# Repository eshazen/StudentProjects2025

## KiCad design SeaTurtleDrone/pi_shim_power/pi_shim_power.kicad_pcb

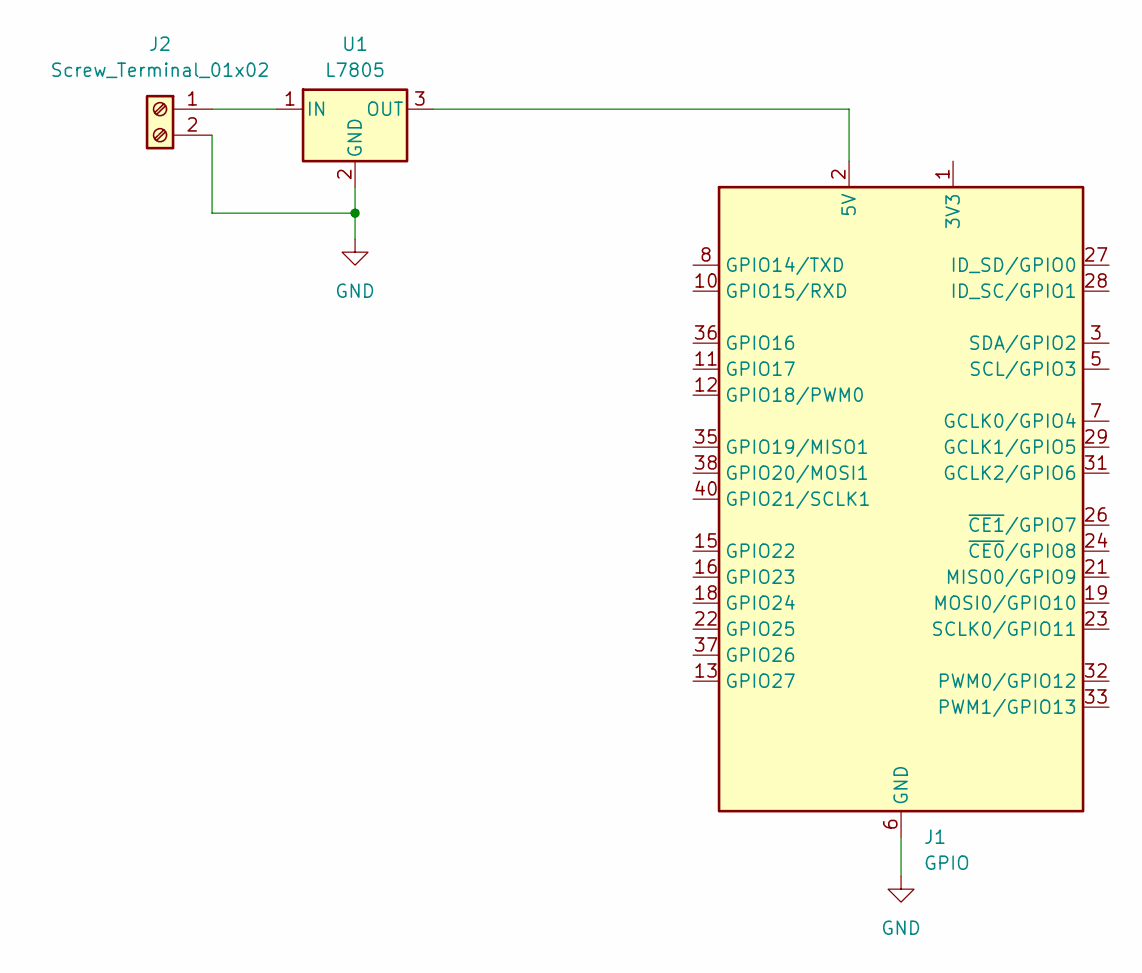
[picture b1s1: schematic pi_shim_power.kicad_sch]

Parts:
J1: GPIO; PinSocket_2x20_P2.54mm_Vertical
J2: Screw_Terminal_01x02; TerminalBlock_MetzConnect_Type055_RT01502HDWU_1x02_P5.00mm_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
U1: L7805; PinHeader_1x03_P2.54mm_Horizontal

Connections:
GND: J1.6 (GND), J1.9 (GND), J1.14 (GND), J1.20 (GND), J1.25 (GND), J1.30 (GND), J1.34 (GND), J1.39 (GND), J2.2, U1.2 (GND)
unnamed: J1.1 (3V3), J1.17 (3V3)
unnamed: J2.1, U1.1 (IN)
unnamed: J1.2 (5V), J1.4 (5V), U1.3 (OUT)

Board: 2 copper layers, 5 parts (1 on the bottom side), 4 nets, no tracks yet.

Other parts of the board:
MH1, MH2: MountingHole_2.7mm_M2.5

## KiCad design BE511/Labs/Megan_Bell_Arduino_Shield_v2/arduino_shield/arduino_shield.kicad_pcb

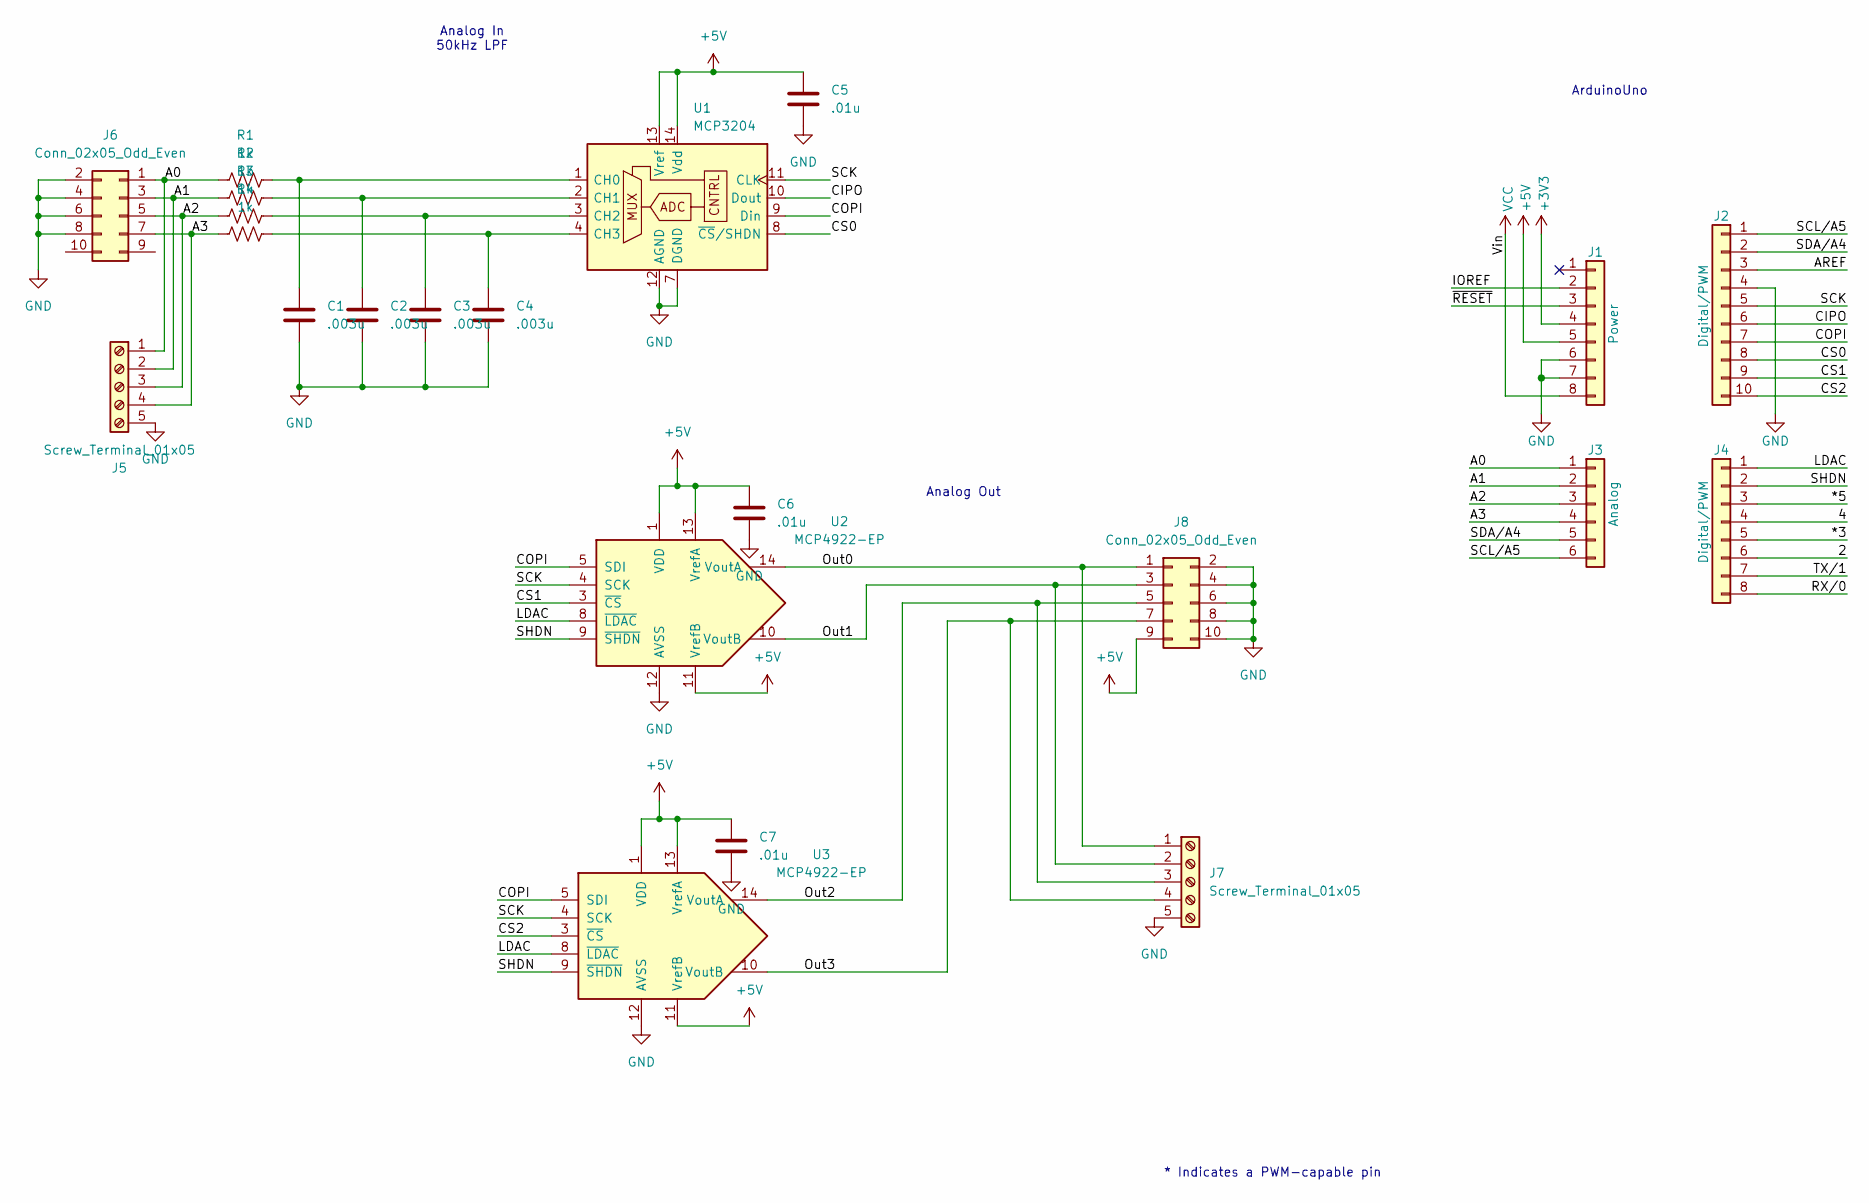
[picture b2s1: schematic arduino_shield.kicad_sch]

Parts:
C1, C2, C3, C4: .003u; C_Disc_D10.0mm_W2.5mm_P5.00mm
C5, C6, C7: .01u; C_Disc_D10.0mm_W2.5mm_P5.00mm
J1: Power; PinSocket_1x08_P2.54mm_Vertical
J2: Digital/PWM; PinSocket_1x10_P2.54mm_Vertical
J3: Analog; PinSocket_1x06_P2.54mm_Vertical
J4: Digital/PWM; PinSocket_1x08_P2.54mm_Vertical
J5, J7: Screw_Terminal_01x05; PinSocket_1x05_P2.54mm_Horizontal
J6, J8: Conn_02x05_Odd_Even; PinSocket_2x05_P2.54mm_Vertical
R1, R2, R3, R4: 1k; R_0805_2012Metric_Pad1.20x1.40mm_HandSolder
U1: MCP3204; DIP-14_W7.62mm
U2, U3: MCP4922-EP; DIP-14_W7.62mm

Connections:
+3V3: J1.4
+5V: C5.1, C6.1, C7.1, J1.5, J8.9, U1.13 (Vref), U1.14 (Vdd), U2.1 (VDD), U2.11 (VrefB), U2.13 (VrefA), U3.1 (VDD), U3.11 (VrefB), U3.13 (VrefA)
/2: J4.6
/4: J4.4
/*3: J4.5
/*5: J4.3
/A0: J3.1, J5.1, J6.1, R1.1
/A1: J3.2, J5.2, J6.3, R2.1
/A2: J3.3, J5.3, J6.5, R3.1
/A3: J3.4, J5.4, J6.7, R4.1
/AREF: J2.3
/CIPO: J2.6, U1.10 (Dout)
/COPI: J2.7, U1.9 (Din), U2.5 (SDI), U3.5 (SDI)
/CS0: J2.8, U1.8 (~CS/SHDN)
/CS1: J2.9, U2.3 (~CS)
/CS2: J2.10, U3.3 (~CS)
/IOREF: J1.2
/LDAC: J4.1, U2.8 (~LDAC), U3.8 (~LDAC)
/Out0: J7.1, J8.1, U2.14 (VoutA)
/Out1: J7.2, J8.3, U2.10 (VoutB)
/Out2: J7.3, J8.5, U3.14 (VoutA)
/Out3: J7.4, J8.7, U3.10 (VoutB)
/RX/0: J4.8
/SCK: J2.5, U1.11 (CLK), U2.4 (SCK), U3.4 (SCK)
/SCL/A5: J2.1, J3.6
/SDA/A4: J2.2, J3.5
/SHDN: J4.2, U2.9 (~SHDN), U3.9 (~SHDN)
/TX/1: J4.7
/~RESET: J1.3
GND: C1.2, C2.2, C3.2, C4.2, C5.2, C6.2, C7.2, J1.6, J1.7, J2.4, J5.5, J6.2, J6.4, J6.6, J6.8, J7.5, J8.2, J8.4, J8.6, J8.8, J8.10, U1.7 (DGND), U1.12 (AGND), U2.12 (AVSS), U3.12 (AVSS)
unnamed: C1.1, R1.2, U1.1 (CH0)
unnamed: C2.1, R2.2, U1.2 (CH1)
unnamed: C3.1, R3.2, U1.3 (CH2)
unnamed: C4.1, R4.2, U1.4 (CH3)
VCC: J1.8

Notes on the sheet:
ArduinoUno
Analog Out
* Indicates a PWM-capable pin
Analog In 50kHz LPF

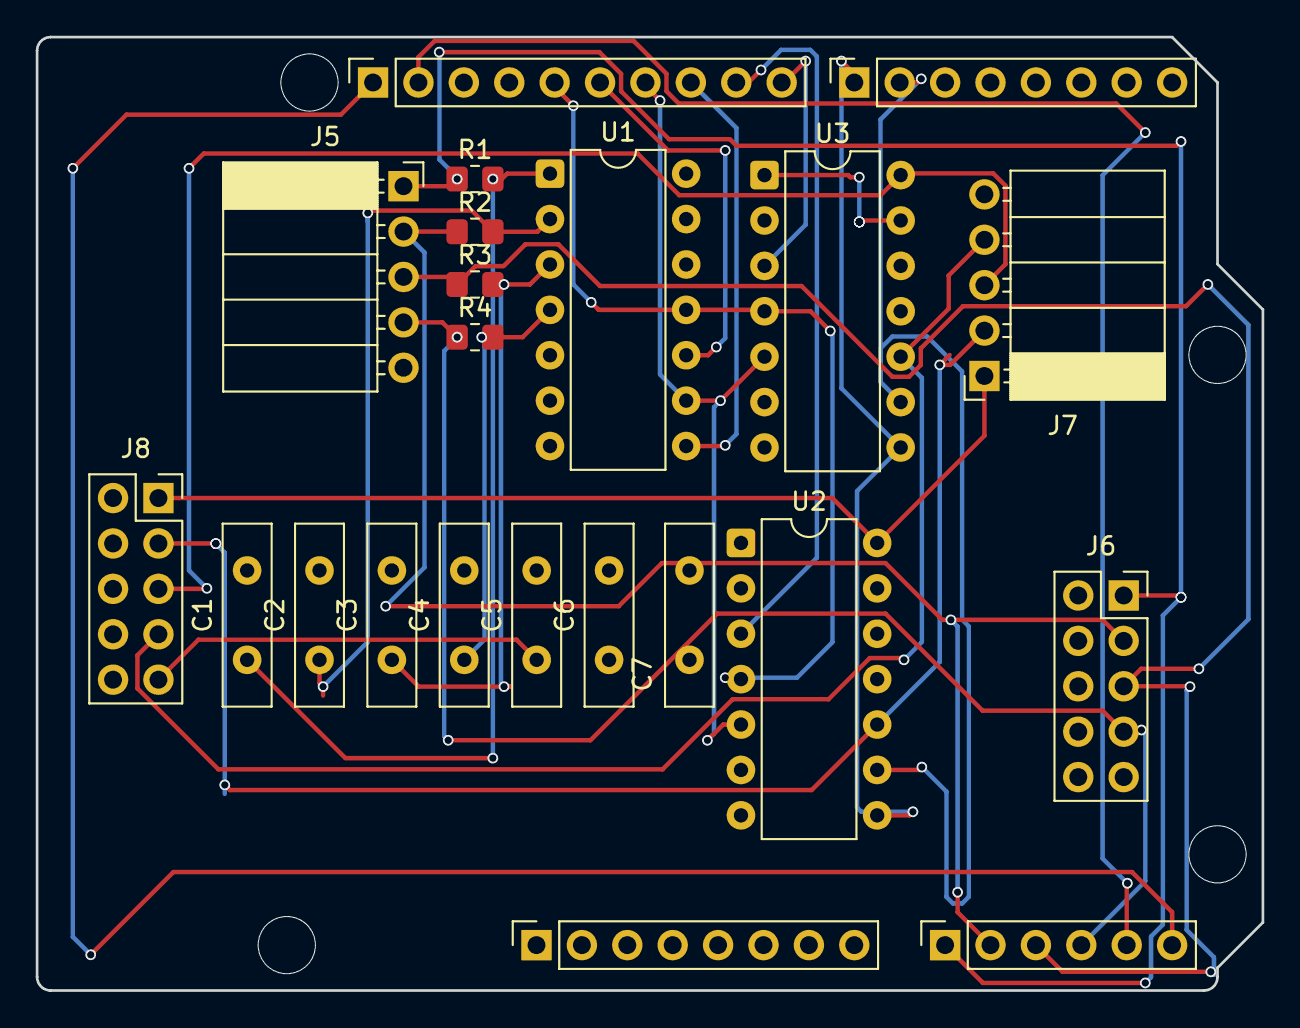
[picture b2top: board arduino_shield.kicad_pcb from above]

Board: 4 copper layers, 68.6 x 53.3 mm, 26 parts (0 on the bottom side), 24 nets.

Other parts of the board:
MH1, MH2, MH3, MH4: MountingHole_3.2mm

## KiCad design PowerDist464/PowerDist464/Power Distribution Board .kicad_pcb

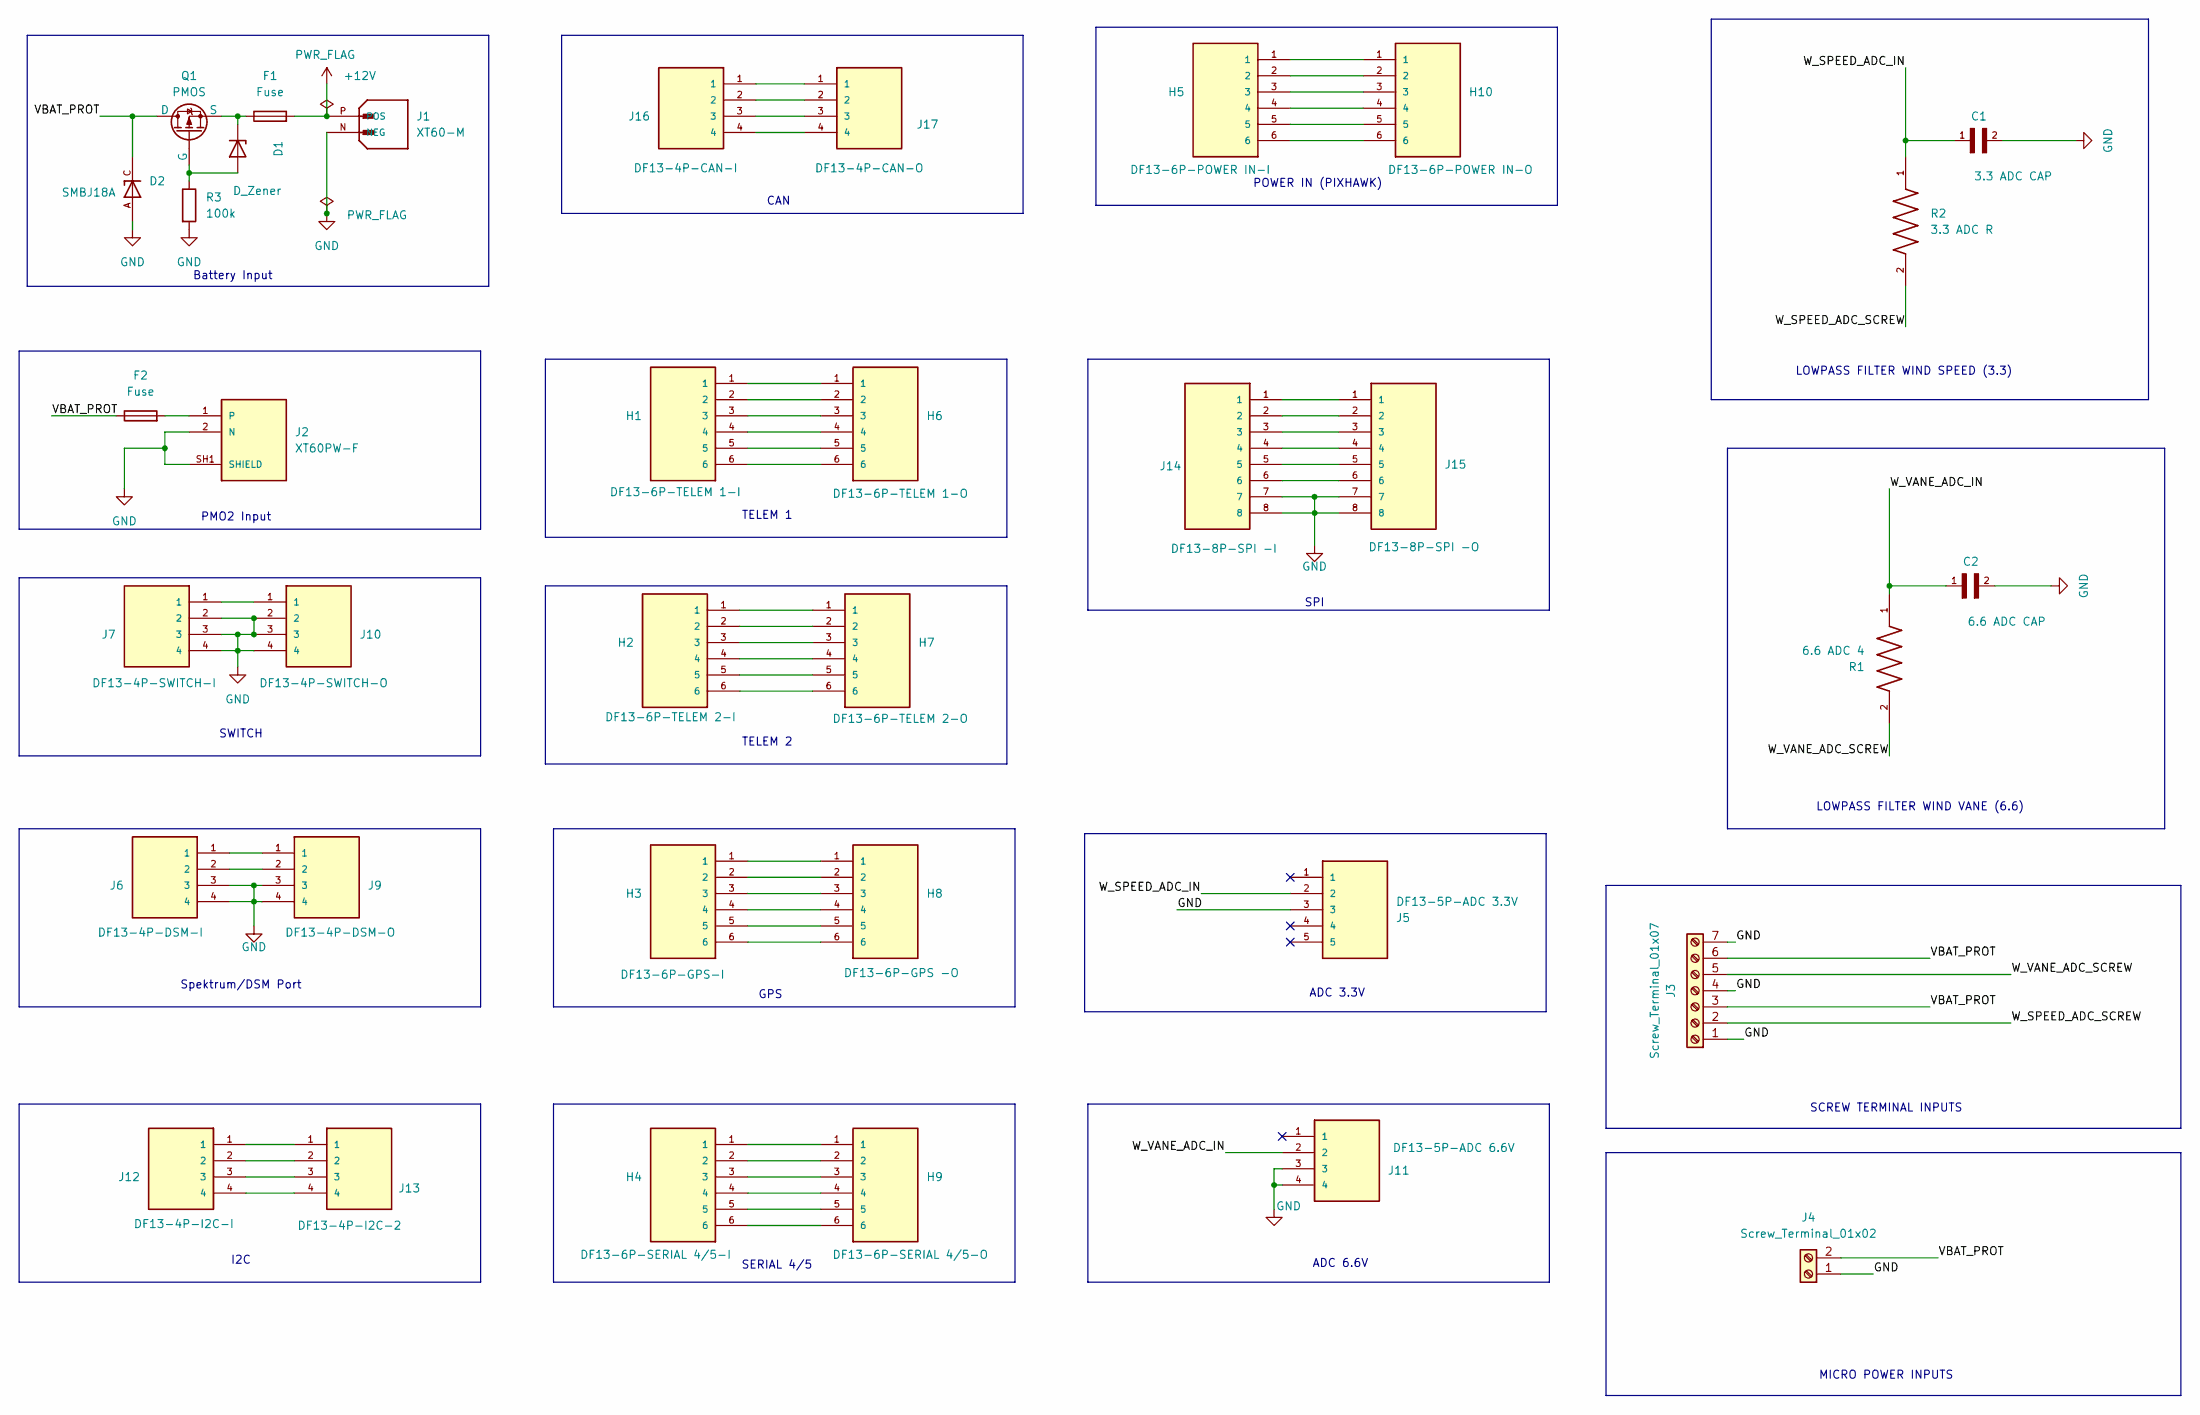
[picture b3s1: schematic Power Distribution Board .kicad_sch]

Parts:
C1: 3.3 ADC CAP; CAPC2012X145N
C2: 6.6 ADC CAP; CAPC2012X145N
D1: D_Zener; DIO_PMEG3020EH_115
D2: SMBJ18A; DIOM4336X265N; PARTREV F2102
F1, F2: Fuse; FUSE_3568-10
H1: DF13-6P-TELEM 1-I; SHDR6W35P0X125_1X6_915X340X430; MOUSER_PART_NUMBER 798-DF13-6P-1.25DSA
H2: DF13-6P-TELEM 2-I; SHDR6W35P0X125_1X6_915X340X430; MOUSER_PART_NUMBER 798-DF13-6P-1.25DSA
H3: DF13-6P-GPS-I; SHDR6W35P0X125_1X6_915X340X430; MOUSER_PART_NUMBER 798-DF13-6P-1.25DSA
H4: DF13-6P-SERIAL 4/5-I; SHDR6W35P0X125_1X6_915X340X430; MOUSER_PART_NUMBER 798-DF13-6P-1.25DSA
H5: DF13-6P-POWER IN-I; SHDR6W35P0X125_1X6_915X340X430; MOUSER_PART_NUMBER 798-DF13-6P-1.25DSA
H6: DF13-6P-TELEM 1-O; SHDR6W35P0X125_1X6_915X340X430; MOUSER_PART_NUMBER 798-DF13-6P-1.25DSA
H7: DF13-6P-TELEM 2-O; SHDR6W35P0X125_1X6_915X340X430; MOUSER_PART_NUMBER 798-DF13-6P-1.25DSA
H8: DF13-6P-GPS -O; SHDR6W35P0X125_1X6_915X340X430; MOUSER_PART_NUMBER 798-DF13-6P-1.25DSA
H9: DF13-6P-SERIAL 4/5-O; SHDR6W35P0X125_1X6_915X340X430; MOUSER_PART_NUMBER 798-DF13-6P-1.25DSA
H10: DF13-6P-POWER IN-O; SHDR6W35P0X125_1X6_915X340X430; MOUSER_PART_NUMBER 798-DF13-6P-1.25DSA
J1: XT60-M; AMASS_XT60-M; PARTREV V1.2
J2: XT60PW-F; AMASS_XT60PW-F; PARTREV 1.2
J3: Screw_Terminal_01x07; TerminalBlock_MaiXu_MX126-5.0-07P_1x07_P5.00mm
J4: Screw_Terminal_01x02; TerminalBlock_MaiXu_MX126-5.0-02P_1x02_P5.00mm
J5: DF13-5P-ADC 3.3V; DF135P125DSA; MOUSER_PART_NUMBER 798-DF13-5P-1.25DSA
J6: DF13-4P-DSM-I; DF134P125DSA; MOUSER_PART_NUMBER 798-DF13-4P-1.25DSA
J7: DF13-4P-SWITCH-I; DF134P125DSA; MOUSER_PART_NUMBER 798-DF13-4P-1.25DSA
J9: DF13-4P-DSM-O; DF134P125DSA; MOUSER_PART_NUMBER 798-DF13-4P-1.25DSA
J10: DF13-4P-SWITCH-O; DF134P125DSA; MOUSER_PART_NUMBER 798-DF13-4P-1.25DSA
J11: DF13-5P-ADC 6.6V; DF134P125DSA; MOUSER_PART_NUMBER 798-DF13-4P-1.25DSA
J12: DF13-4P-I2C-I; DF134P125DSA; MOUSER_PART_NUMBER 798-DF13-4P-1.25DSA
J13: DF13-4P-I2C-2; DF134P125DSA; MOUSER_PART_NUMBER 798-DF13-4P-1.25DSA
J14: DF13-8P-SPI -I; DF138P125DSA; MOUSER_PART_NUMBER 798-DF13-8P-1.25DSA
J15: DF13-8P-SPI -O; DF138P125DSA; MOUSER_PART_NUMBER 798-DF13-8P-1.25DSA
J16: DF13-4P-CAN-I; DF134P125DSA; MOUSER_PART_NUMBER 798-DF13-4P-1.25DSA
J17: DF13-4P-CAN-O; DF134P125DSA; MOUSER_PART_NUMBER 798-DF13-4P-1.25DSA
Q1: PMOS; TO228P998X235-3N-2-V
R1: 6.6 ADC 4; RESC2012X60N
R2: 3.3 ADC R; RESC2012X60N
R3: 100k; R_Axial_DIN0204_L3.6mm_D1.6mm_P5.08mm_Horizontal

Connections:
+12V: F1.2, J1.P (POS)
/VBAT_PROT: D2.C, F2.1, J3.3, J3.6, J4.2, Q1.1 (D)
/W_SPEED_ADC_IN: C1.1, J5.2, R2.1
/W_SPEED_ADC_SCREW: J3.2, R2.2
/W_VANE_ADC_IN: C2.1, J11.2, R1.1
/W_VANE_ADC_SCREW: J3.5, R1.2
GND: C1.2, C2.2, D2.A, J1.N (NEG), J2.2 (N), J2.SH1 (SHIELD), J2.SH2 (SHIELD), J3.1, J3.4, J3.7, J4.1, J5.3, J6.3, J6.4, J7.2, J7.3, J7.4, J9.3, J9.4, J10.2, J10.3, J10.4, J11.3, J11.4, J14.7, J14.8, J15.7, J15.8, R3.2
unnamed: H1.1, H6.1
unnamed: H1.2, H6.2
unnamed: H1.3, H6.3
unnamed: H1.4, H6.4
unnamed: H1.5, H6.5
unnamed: H1.6, H6.6
unnamed: H2.1, H7.1
unnamed: H2.2, H7.2
unnamed: H2.3, H7.3
unnamed: H2.4, H7.4
unnamed: H2.5, H7.5
unnamed: H2.6, H7.6
unnamed: H3.1, H8.1
unnamed: H3.2, H8.2
unnamed: H3.3, H8.3
unnamed: H3.4, H8.4
unnamed: H3.5, H8.5
unnamed: H3.6, H8.6
unnamed: H4.1, H9.1
unnamed: H4.2, H9.2
unnamed: H4.3, H9.3
unnamed: H4.4, H9.4
unnamed: H4.5, H9.5
unnamed: H4.6, H9.6
unnamed: H5.1, H10.1
unnamed: H5.2, H10.2
unnamed: H5.3, H10.3
unnamed: H5.4, H10.4
unnamed: H5.5, H10.5
unnamed: H5.6, H10.6
unnamed: F2.2, J2.1
unnamed: J6.1, J9.1
unnamed: J6.2, J9.2
unnamed: J7.1, J10.1
unnamed: J12.1, J13.1
unnamed: J12.2, J13.2
unnamed: J12.3, J13.3
unnamed: J12.4, J13.4
unnamed: J14.1, J15.1
unnamed: J14.2, J15.2
unnamed: J14.3, J15.3
unnamed: J14.4, J15.4
unnamed: J14.5, J15.5
unnamed: J14.6, J15.6
unnamed: J16.1, J17.1
unnamed: J16.2, J17.2
unnamed: J16.3, J17.3
unnamed: J16.4, J17.4
unnamed: D1.2, Q1.2 (G), R3.1
unnamed: D1.1, F1.1, Q1.3 (S)

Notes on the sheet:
LOWPASS FILTER WIND SPEED (3.3)
SCREW TERMINAL INPUTS
GPS
LOWPASS FILTER WIND VANE (6.6)
I2C
MICRO POWER INPUTS
ADC 3.3V
Battery Input
Spektrum/DSM Port
TELEM 2
SPI
SERIAL 4/5
CAN
SWITCH
TELEM 1
ADC 6.6V
POWER IN (PIXHAWK)
PMO2 Input

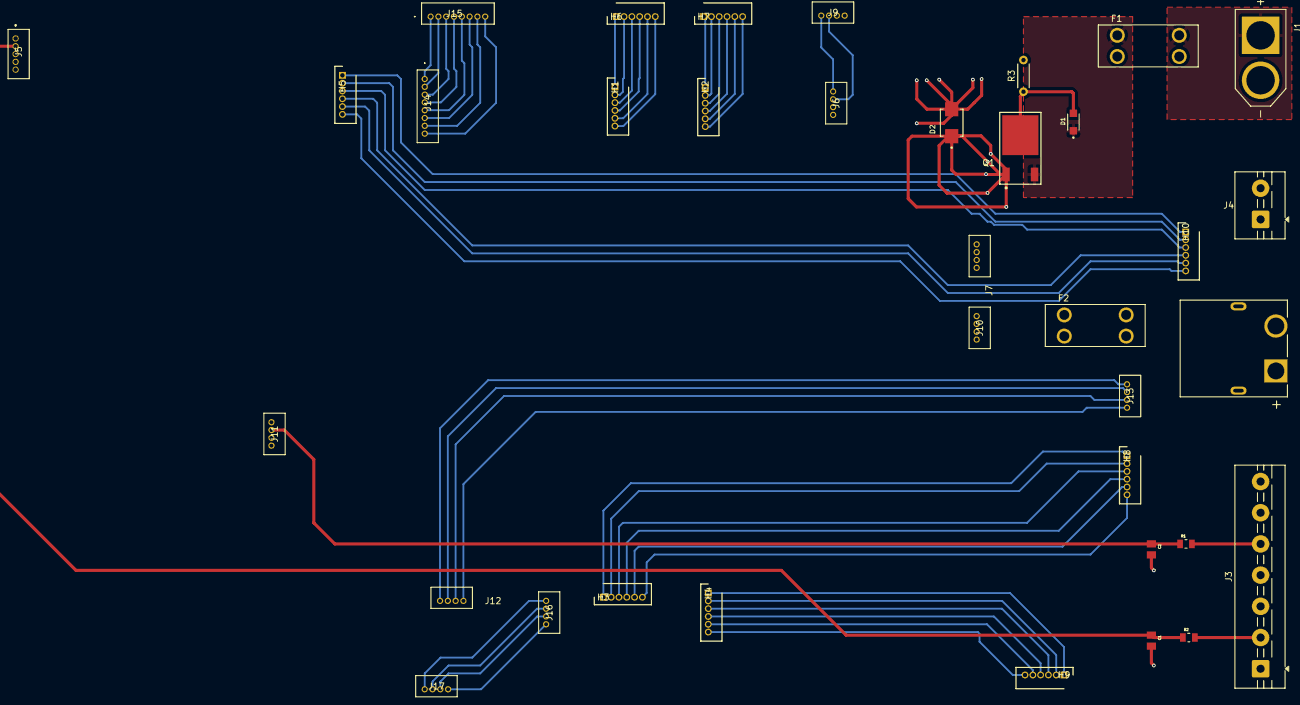
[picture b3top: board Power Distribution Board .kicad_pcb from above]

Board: 4 copper layers, 36 parts (0 on the bottom side), 57 nets.

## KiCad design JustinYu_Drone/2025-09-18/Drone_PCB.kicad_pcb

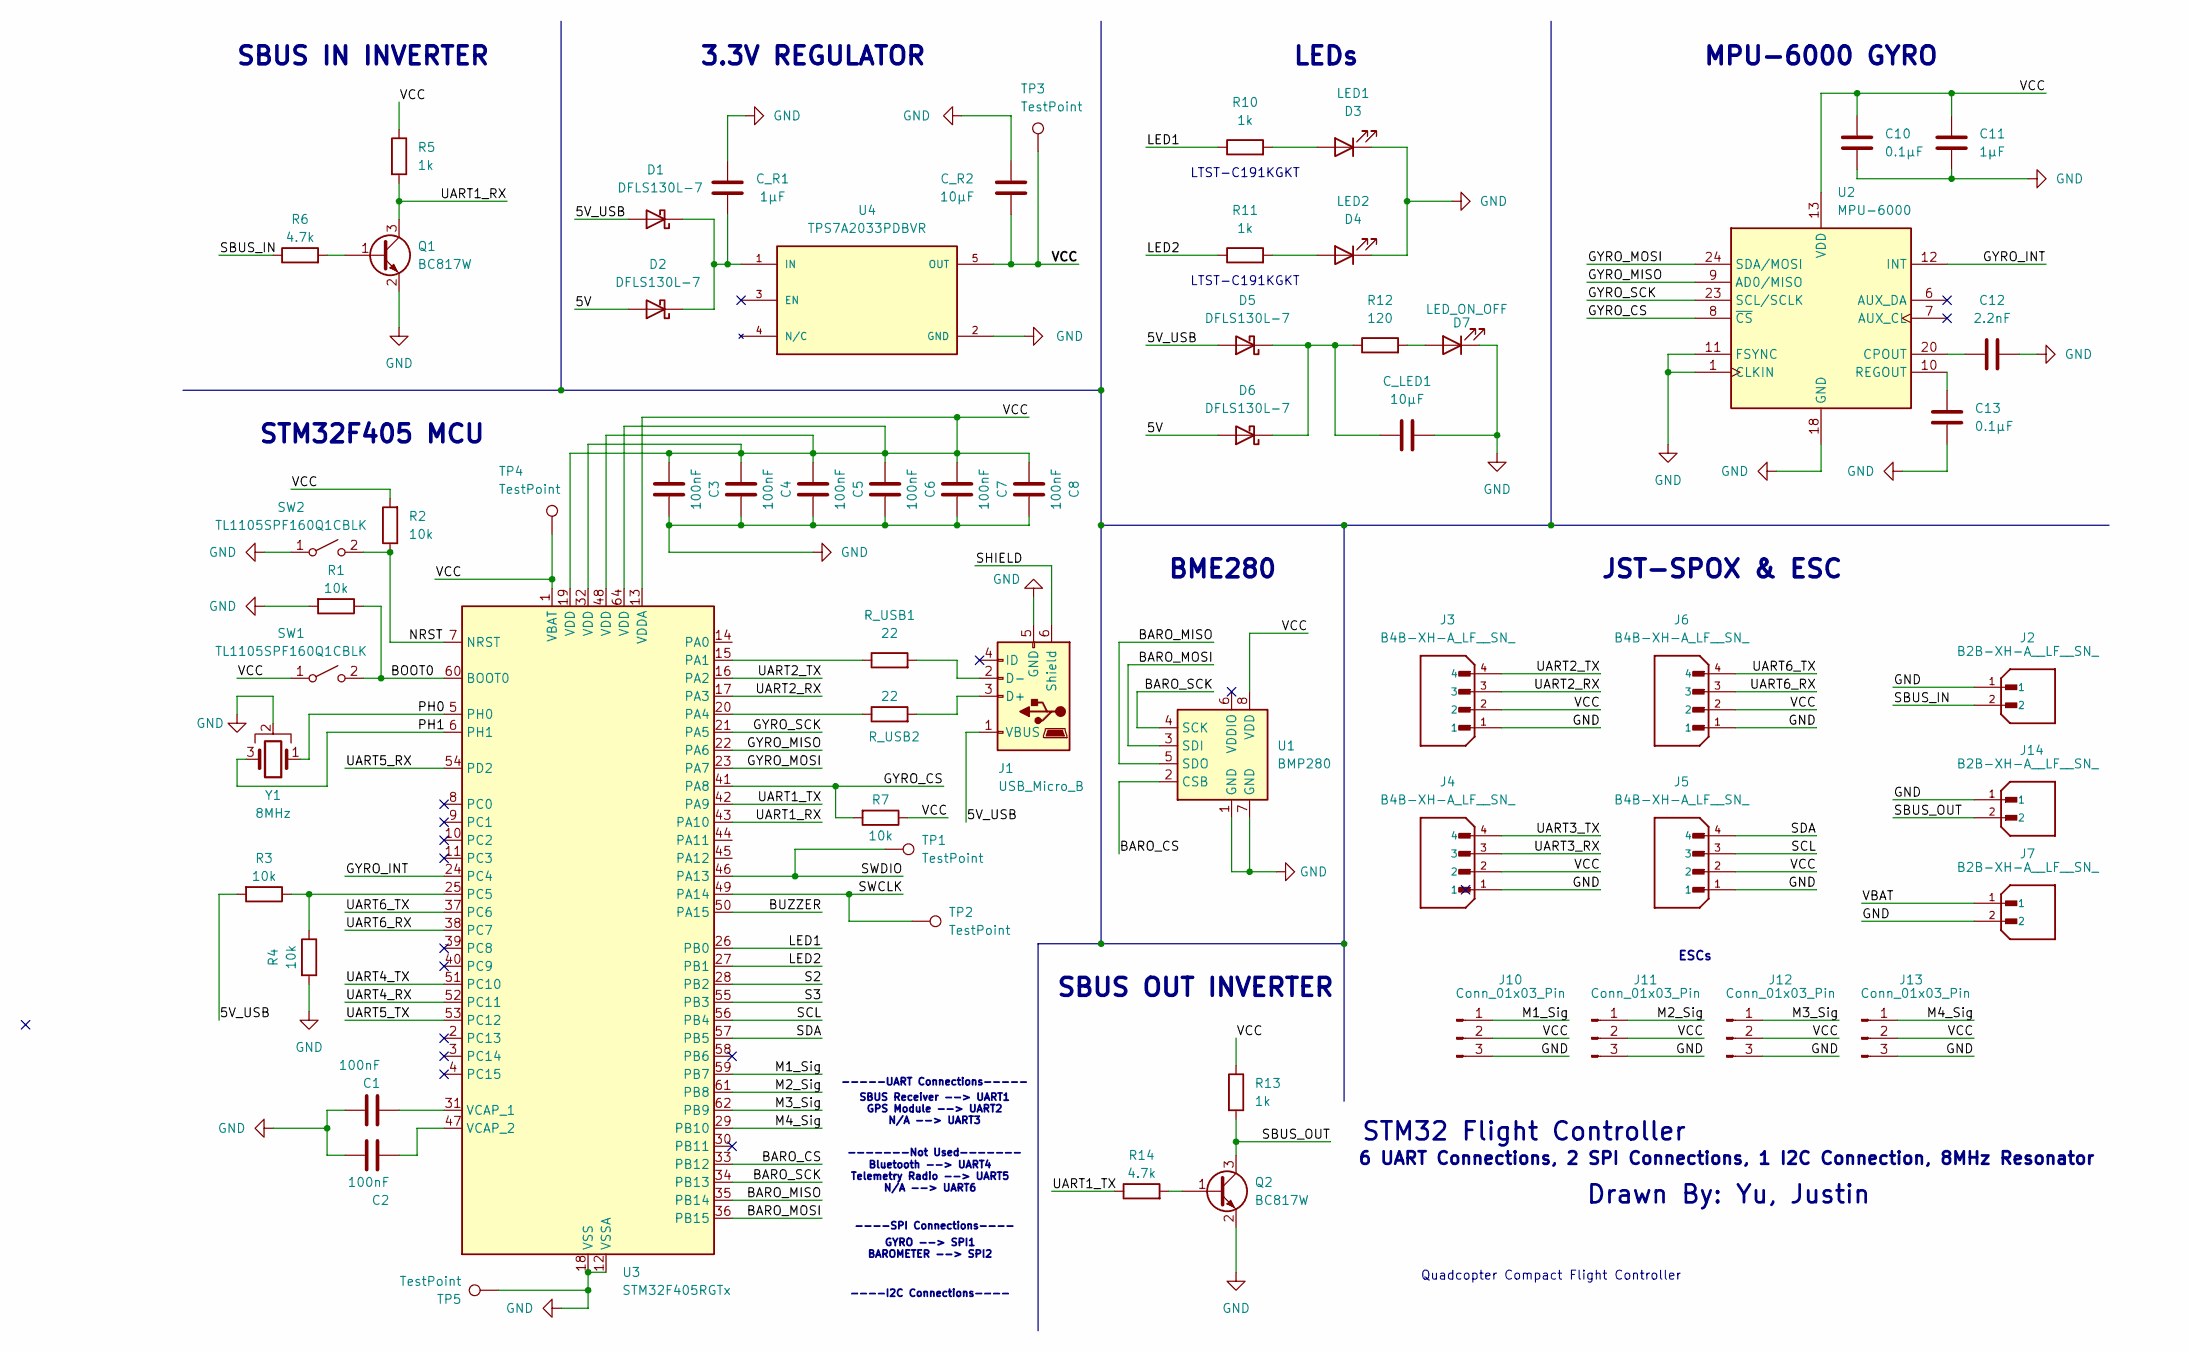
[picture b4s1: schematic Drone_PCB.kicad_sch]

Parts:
C1, C2, C3, C4, C5, C6, C7, C8: 100nF; CC0603KRX7R8BB104
C10, C13: 0.1µF; CC0603KRX7R8BB104
C11: 1µF; CC0603KRX7R8BB104
C12: 2.2nF; CC0603KRX7R8BB104
C_LED1: 10μF; CC0603KRX7R8BB104
C_R1: 1µF; CC0603KRX7R8BB104
C_R2: 10µF; CC0603KRX7R8BB104
D1, D2, D5, D6: DFLS130L-7
D3: LED1; LTST-C191KGKT
D4: LED2; LTST-C191KGKT
D7: LED_ON_OFF; LTST-C191KGKT
J1: USB_Micro_B; USB_C
J2, J14: B2B-XH-A__LF__SN_; PinSocket_1x02_P2.54mm_Vertical; PARTREV N/A
J3, J4, J5, J6: B4B-XH-A_LF__SN_; JST_B4B; PARTREV 7/4/21
J7: B2B-XH-A__LF__SN_; JST_B2B-XH-A__LF__SN_; PARTREV N/A
J10, J11, J12, J13: Conn_01x03_Pin; PinSocket_1x03_P2.54mm_Vertical
Q1, Q2: BC817W
R1, R2, R3, R4, R7: 10k; R_0603_1608Metric_Pad0.98x0.95mm_HandSolder
R5, R10, R11, R13: 1k; R_0603_1608Metric_Pad0.98x0.95mm_HandSolder
R6, R14: 4.7k; R_0603_1608Metric_Pad0.98x0.95mm_HandSolder
R12: 120; R_0603_1608Metric_Pad0.98x0.95mm_HandSolder
R_USB1, R_USB2: 22; R_0603_1608Metric_Pad0.98x0.95mm_HandSolder
SW1, SW2: TL1105SPF160Q1CBLK; KMR221G LFS
TP1, TP2, TP3, TP4, TP5: TestPoint; TestPoint_Pad_1.0x1.0mm
U1: BMP280
U2: MPU-6000; InvenSense_QFN-24_4x4mm_P0.5mm
U3: STM32F405RGTx; LQFP-64_10x10mm_P0.5mm
U4: TPS7A2033PDBVR; PARTREV H
Y1: 8MHz; ABLS-8.000MHZ-B4-T

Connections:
/5V: D2.2 (A), D6.2 (A)
/5V_USB: D1.2 (A), D5.2 (A), J1.1 (VBUS), R3.2
/BARO_CS: U1.2 (CSB), U3.33 (PB12)
/BARO_MISO: U1.5 (SDO), U3.35 (PB14)
/BARO_MOSI: U1.3 (SDI), U3.36 (PB15)
/BARO_SCK: U1.4 (SCK), U3.34 (PB13)
/BOOT0: R1.1, SW1.2 (B), U3.60 (BOOT0)
/BUZZER: U3.50 (PA15)
/GYRO_CS: R7.2, U2.8 (~CS), U3.41 (PA8)
/GYRO_INT: U2.12 (INT), U3.24 (PC4)
/GYRO_MISO: U2.9 (AD0/MISO), U3.22 (PA6)
/GYRO_MOSI: U2.24 (SDA/MOSI), U3.23 (PA7)
/GYRO_SCK: U2.23 (SCL/SCLK), U3.21 (PA5)
/LED1: R10.1, U3.26 (PB0)
/LED2: R11.1, U3.27 (PB1)
/M1_Sig: J10.1, U3.59 (PB7)
/M2_Sig: J11.1, U3.61 (PB8)
/M3_Sig: J12.1, U3.62 (PB9)
/M4_Sig: J13.1, U3.29 (PB10)
/NRST: R2.1, SW2.2 (B), U3.7 (NRST)
/PH0: U3.5 (PH0), Y1.1
/S2: U3.28 (PB2)
/S3: U3.55 (PB3)
/SBUS_IN: J2.2, R6.1
/SBUS_OUT: J14.2, Q2.3 (C), R13.2
/SCL: J5.3, U3.56 (PB4)
/SDA: J5.4, U3.57 (PB5)
/SWCLK: TP2.1, U3.49 (PA14)
/SWDIO: TP1.1, U3.46 (PA13)
/UART1_RX: Q1.3 (C), R5.2, U3.43 (PA10)
/UART1_TX: R14.1, U3.42 (PA9)
/UART2_RX: J3.3, U3.17 (PA3)
/UART2_TX: J3.4, U3.16 (PA2)
/UART3_RX: J4.3
/UART3_TX: J4.4
/UART4_RX: U3.52 (PC11)
/UART4_TX: U3.51 (PC10)
/UART5_RX: U3.54 (PD2)
/UART5_TX: U3.53 (PC12)
/UART6_RX: J6.3, U3.38 (PC7)
/UART6_TX: J6.4, U3.37 (PC6)
/VCC: C3.1, C4.1, C5.1, C6.1, C7.1, C8.2, C10.2, C11.2, C_R2.1, J3.2, J4.2, J5.2, J6.2, J10.2, J11.2, J12.2, J13.2, R2.2, R5.1, R7.1, R13.1, SW1.1 (A), TP3.1, TP4.1, U1.8 (VDD), U2.13 (VDD), U3.1 (VBAT), U3.13 (VDDA), U3.19 (VDD), U3.32 (VDD), U3.48 (VDD), U3.64 (VDD), U4.5 (OUT)
unnamed: C_R1.1, D1.1 (K), D2.1 (K), U4.1 (IN)
unnamed: D3.2 (A), R10.2
unnamed: D4.2 (A), R11.2
unnamed: C_LED1.2, D5.1 (K), D6.1 (K), R12.1
unnamed: D7.2 (A), R12.2
unnamed: J1.3 (D+), R_USB2.2
unnamed: J1.2 (D-), R_USB1.2
unnamed: Q1.1 (B), R6.2
unnamed: Q2.1 (B), R14.2
unnamed: C12.2, U2.20 (CPOUT)
unnamed: C13.2, U2.10 (REGOUT)
unnamed: R_USB1.1, U3.15 (PA1)
unnamed: R_USB2.1, U3.20 (PA4)
unnamed: R3.1, R4.1, U3.25 (PC5)
unnamed: C1.1, U3.31 (VCAP_1)
unnamed: C2.1, U3.47 (VCAP_2)

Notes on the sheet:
LTST-C191KGKT
----SPI Connections----
GYRO --> SPI1 BAROMETER --> SPI2
SBUS OUT INVERTER
6 UART Connections, 2 SPI Connections, 1 I2C Connection, 8MHz Resonator
3.3V REGULATOR
STM32 Flight Controller
Yu, Justin
SBUS Receiver --> UART1 GPS Module --> UART2 N/A --> UART3
-----UART Connections-----
STM32F405 MCU
----I2C Connections----
BME280
Bluetooth --> UART4 Telemetry Radio --> UART5 N/A --> UART6
Quadcopter Compact Flight Controller
LEDs
-------Not Used-------
JST-SPOX & ESC
MPU-6000 GYRO
ESCs
SBUS IN INVERTER
Drawn By:

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
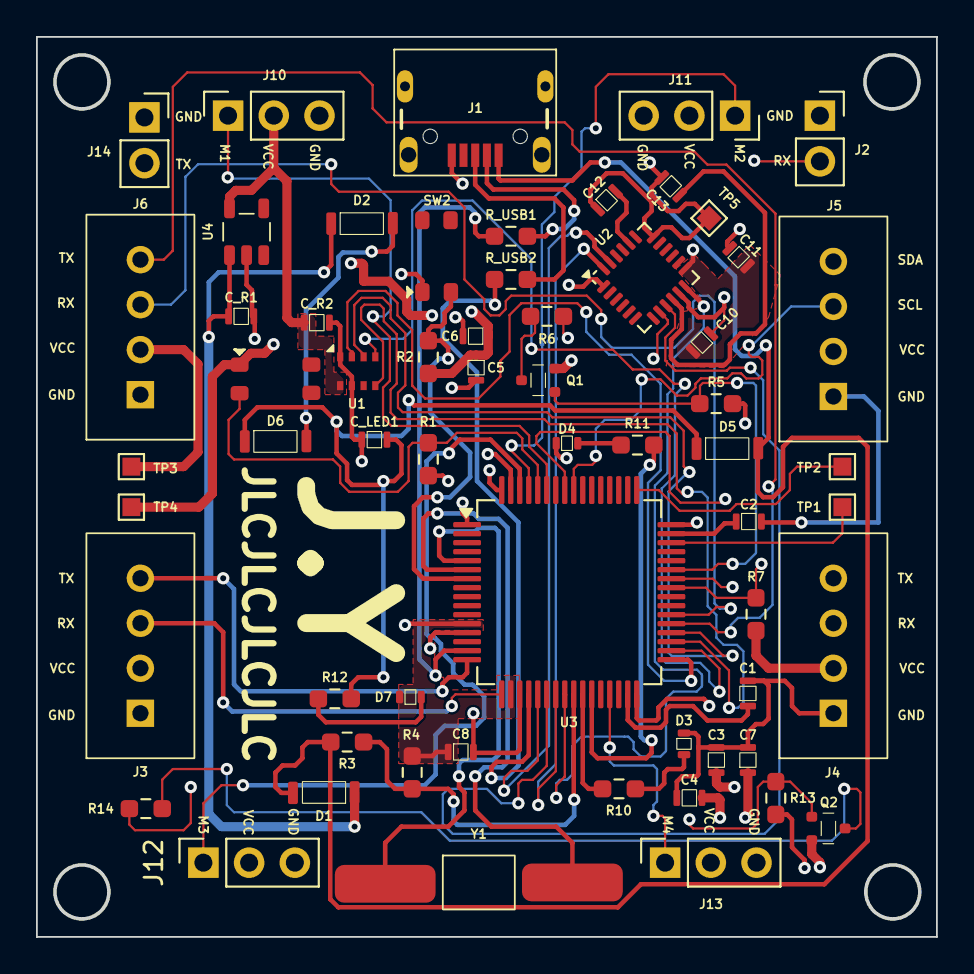
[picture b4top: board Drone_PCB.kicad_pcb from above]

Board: 4 copper layers, 50.0 x 50.0 mm, 61 parts (0 on the bottom side), 51 nets.

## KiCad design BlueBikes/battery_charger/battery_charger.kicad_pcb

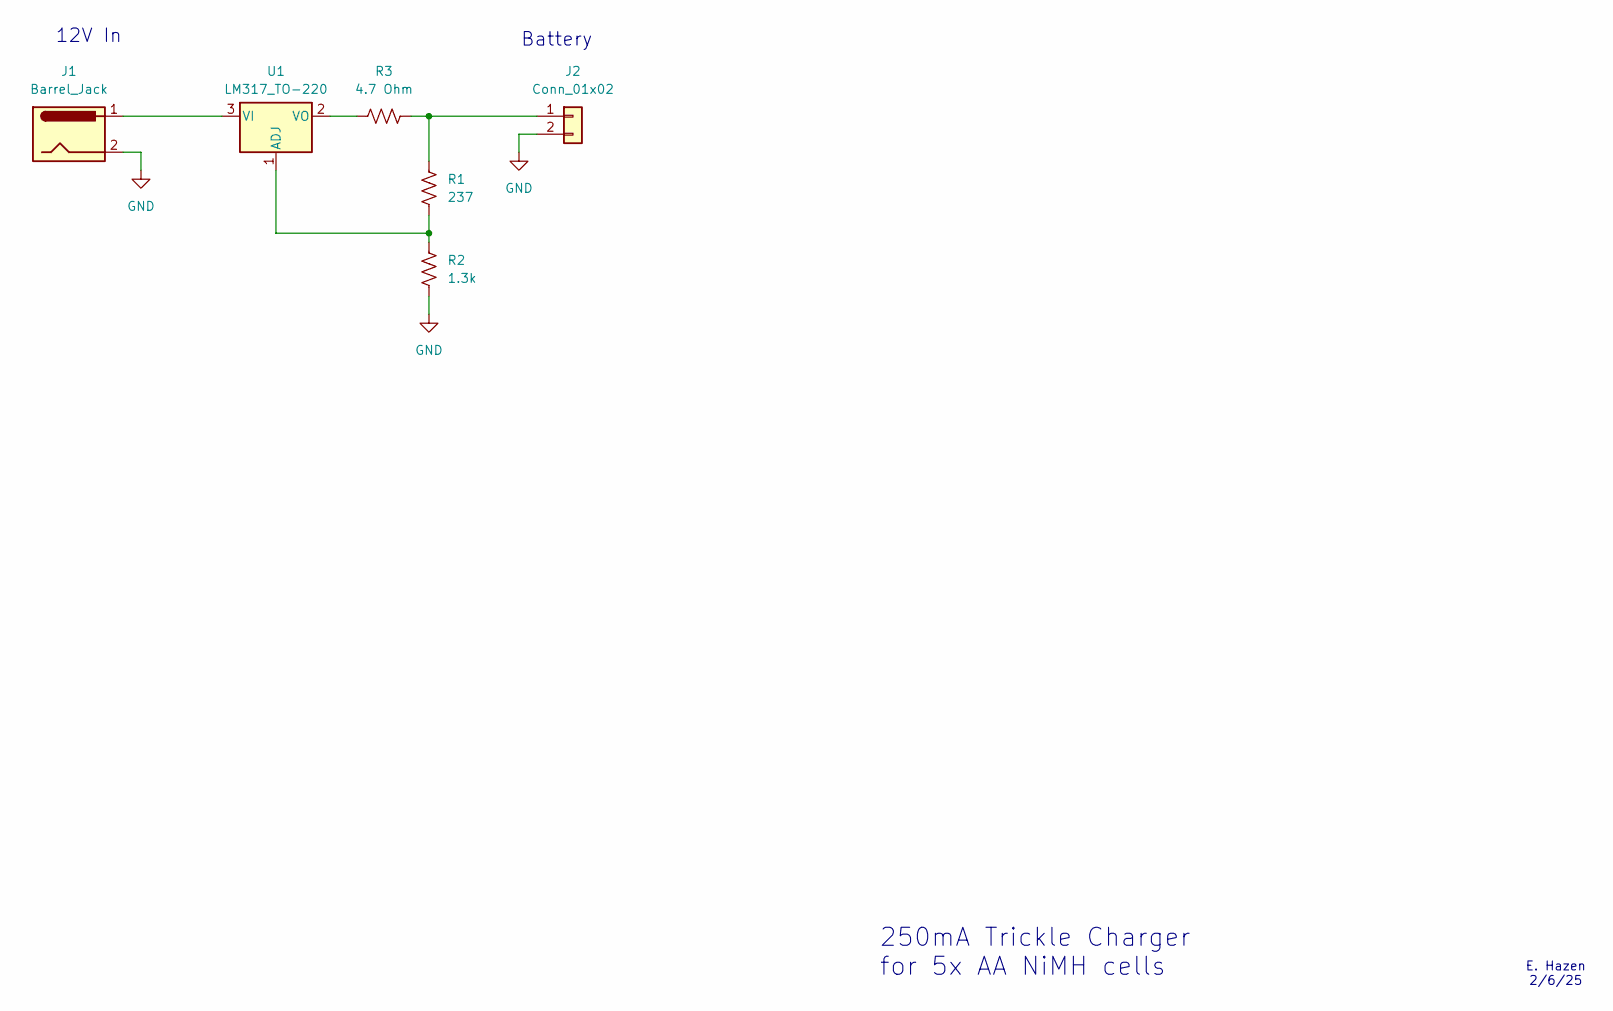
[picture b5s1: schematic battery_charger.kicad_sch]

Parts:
J1: Barrel_Jack; CUI_PJ-002B
J2: Conn_01x02; CUI_PJ-002B
R1: 237; R_Axial_DIN0207_L6.3mm_D2.5mm_P10.16mm_Horizontal
R2: 1.3k; R_Axial_DIN0207_L6.3mm_D2.5mm_P10.16mm_Horizontal
R3: 4.7 Ohm; R_Axial_DIN0207_L6.3mm_D2.5mm_P10.16mm_Horizontal
U1: LM317_TO-220; TO-220-3_Vertical

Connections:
GND: J1.2, J2.2, R2.2
unnamed: J2.1, R1.1, R3.2
unnamed: R1.2, R2.1, U1.1 (ADJ)
unnamed: J1.1, U1.3 (VI)
unnamed: R3.1, U1.2 (VO)

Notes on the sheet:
E. Hazen 2/6/25
250mA Trickle Charger for 5x AA NiMH cells
Battery
12V In

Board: 2 copper layers, 6 parts (0 on the bottom side), 5 nets, no tracks yet.

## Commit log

2025-02-06 3D model
2025-02-06 model update
2025-02-17 simple sprouts
2025-03-05 update all
2025-03-05 minibots
2025-03-31 update various PCB
2025-04-16 Add solar hydrogen code
2025-04-23 hydrogen
2025-04-23 walkman
2025-05-01 save some stuff
2025-05-13 add MCP4922 python code
2025-05-19 camera stuff
2025-05-19 gpt code
2025-05-19 faster GPT code
2025-05-19 more GPT
2025-07-09 thermal wave sensing (Lubner)
2025-09-18 sr design
2025-09-24 notes on aero/sub
2026-02-10 add water sampler
2026-02-10 update water sampler
2026-02-11 stuff
2026-03-03 powerdist
2026-03-19 Robot Coyote example
